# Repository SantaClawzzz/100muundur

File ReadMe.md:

# 100kHz alalisvoolu alandavmuundur

Seoses TalTech projekti raames. Esines probleeme, aga v0 töötas.

* ROE1205S pinout on tagurpidi.
* Üks elektrolüüt on ühtpidi, teine teistpidi.

Saab väiksemalt, vähemalt pugav joota.
Parts list pole vist ka väga kallis.

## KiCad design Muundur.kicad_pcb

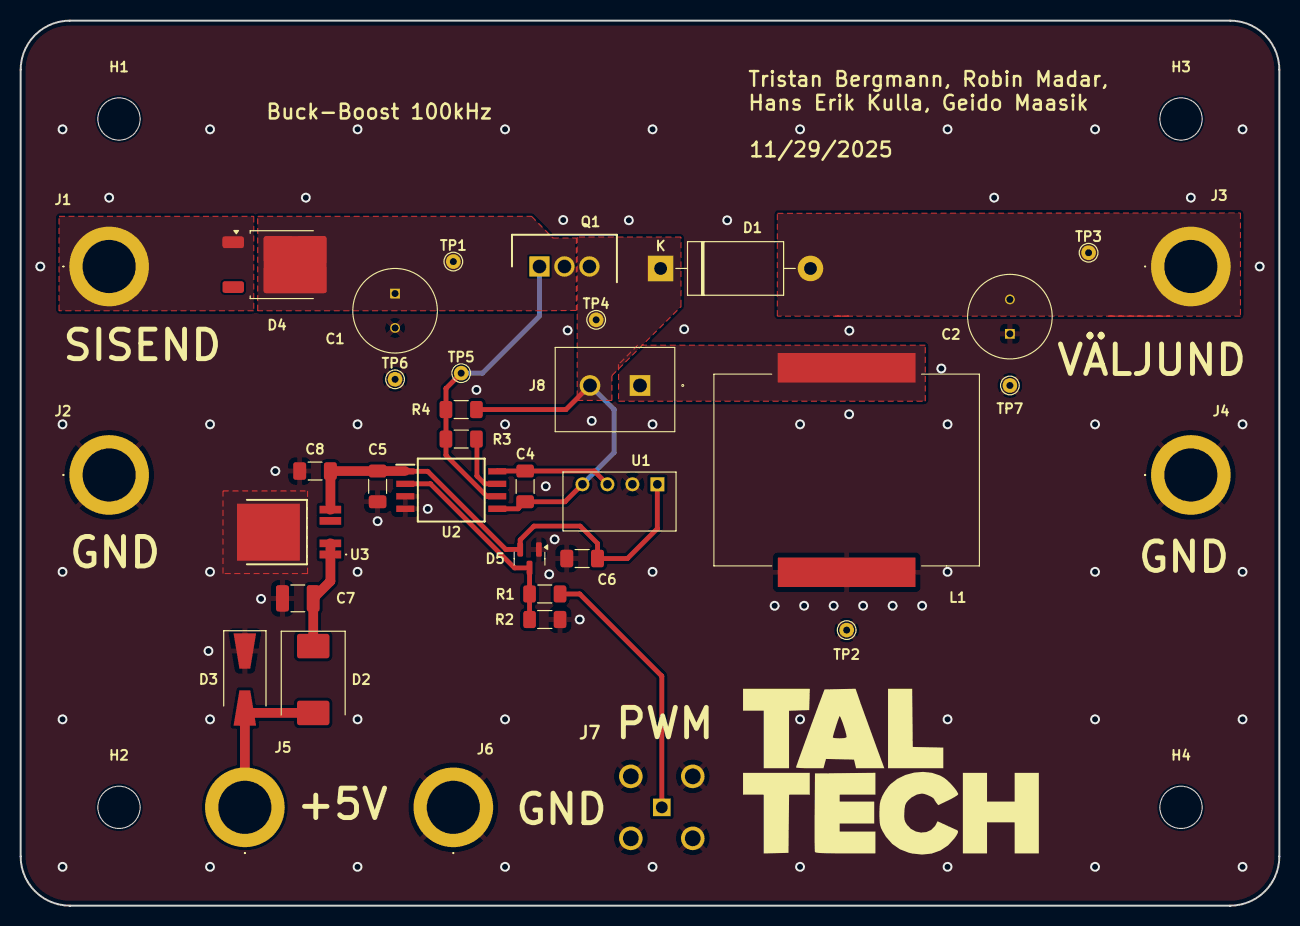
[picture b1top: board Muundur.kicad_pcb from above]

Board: 2 copper layers, 128.0 x 90.0 mm, 40 parts (0 on the bottom side), 14 nets.

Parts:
C1: 82uF; 8mm CAP
C2: 120uF; 8mm CAP
C4, C6: 4.7uF; C_1206_3216Metric_Pad1.33x1.80mm_HandSolder
C5: 100nF; C_1206_3216Metric_Pad1.33x1.80mm_HandSolder
C7: 10uF; C_1210_3225Metric_Pad1.33x2.70mm_HandSolder
C8: 10uF; C_1206_3216Metric_Pad1.33x1.80mm_HandSolder
D1: SR515 A0G; D_DO-201_P15.24mm_Horizontal
D2: B360A-M3/61T; D_SMC
D3: 78-SMBJ26CD-M3/H; D_SMA-SMB_Universal_Handsoldering
D4: VS-50WQ10FNTR-M3; TO-252.2
D5: BAS 70-04; SOT-23
H1, H2, H3, H4: Standoff; MountingHole_4.3mm_M4
J1, J2, J3, J4, J5, J6: 5758
J7: CONBNC001
J8: Terminal_block; 1755736
L1: 150uH; 60B154C
Q1: IRFB4615PBF; TO254P483X1016X1994-3P
R1: 2.2k; R_1206_3216Metric_Pad1.30x1.75mm_HandSolder
R2: 47k; R_1206_3216Metric_Pad1.30x1.75mm_HandSolder
R3: 10R; R_1206_3216Metric_Pad1.30x1.75mm_HandSolder
R4: 10k; R_1206_3216Metric_Pad1.30x1.75mm_HandSolder
TP1, TP2, TP3, TP4, TP5, TP6, TP7: TestPoint; TestPoint_THTPad_D1.5mm_Drill0.7mm
U1: ROE-5012S; ROE1205S
U2: 1ED3122MC12HXUMA1; SOIC127P1030X265-8N
U3: AP7583Q-50D4-13; AP7583Q50D413

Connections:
+5V: C5.1, C6.1, C8.1, D5.2, U1.1 (VIN+), U2.1 (VCC1), U3.5 (VOUT)
+12V: C4.1, U1.3 (VOUT+), U2.8 (VCC2)
+24V: C2.2, D1.2 (A), J3.1, TP3.1
+50V: D4.2 (A), J1.1
/GATE: Q1.2 (G), R3.2, R4.1, TP5.1, U2.6 (CLAMP)
GND: C1.2, C2.1, C5.2, C6.2, C7.2, C8.2, D3.1 (A1), D5.1, J2.1, J4.1, J6.1, J7.2 (GND), J7.3 (GND), J7.4 (GND), J7.5 (GND), L1.2, R2.2, TP2.1, TP6.1, TP7.1, U1.2 (VIN-), U2.3 (IN-), U2.4 (GND1), U3.3 (GND)
GND2: C4.2, D1.1 (K), J8.2, Q1.3 (S), R4.2, TP4.1, U1.4 (VOUT-), U2.5 (VEE2)
IND: J8.1, L1.1
unnamed: D2.2 (A), D3.2 (A2), J5.1
unnamed: C7.1, D2.1 (K), U3.1 (VIN), U3.2 (EN)
unnamed: J7.1 (CON), R1.1
unnamed: D5.3, R1.2, R2.1, U2.2 (IN+)
unnamed: R3.1, U2.7 (OUT)
REV_POL: C1.1, D4.1 (K), Q1.1 (D), TP1.1

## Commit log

2026-05-22 Initial commit, documentation needed
2026-05-23 Final with documentation
